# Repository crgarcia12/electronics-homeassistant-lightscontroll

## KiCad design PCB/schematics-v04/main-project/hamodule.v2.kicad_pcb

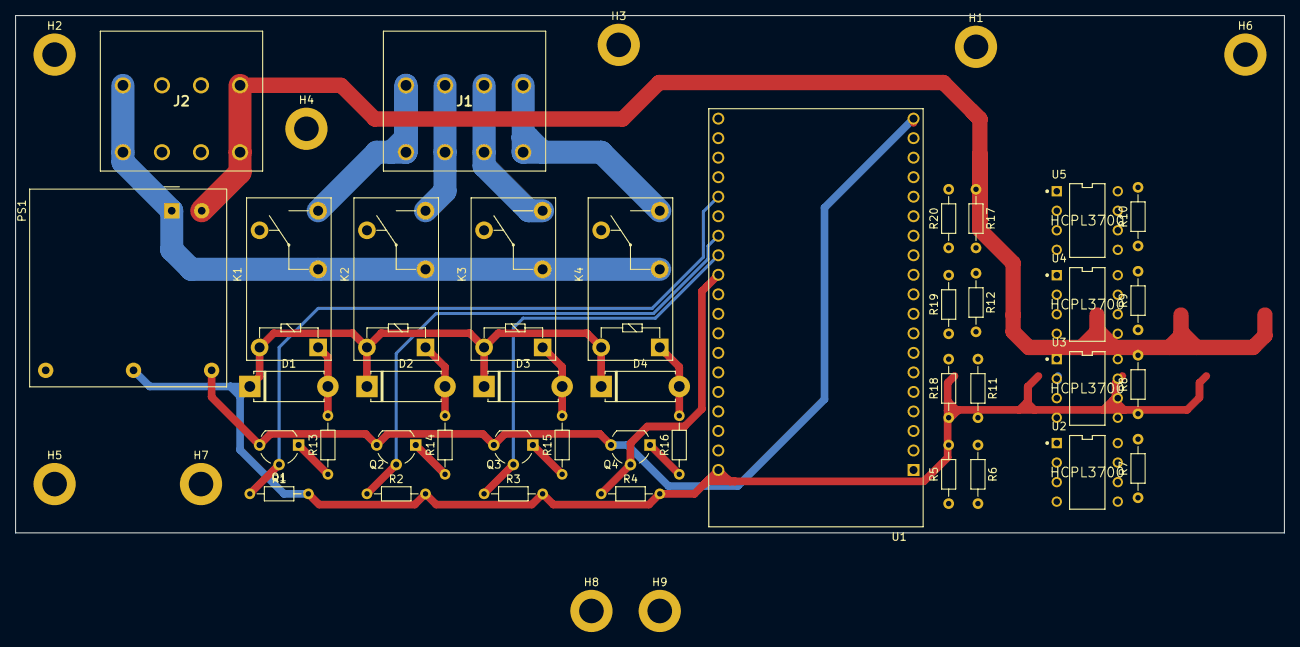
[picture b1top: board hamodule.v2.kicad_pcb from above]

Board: 2 copper layers, 165.1 x 67.3 mm, 49 parts (0 on the bottom side), 34 nets.

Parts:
D1, D2, D3, D4: DIODE; D_5W_P10.16mm_Horizontal
H1, H2, H3, H4, H5, H6, H7, H8, H9: MountingHole_Pad; MountingHole_3.2mm_M3_ISO14580_Pad
J1, J2: 1017505
K1, K2, K3, K4: G5Q-1; Relay_SPDT_Omron-G5Q-1
PS1: RAC05-05SK; Converter_ACDC_RECOM_RAC05-xxSK_THT
Q1, Q2, Q3, Q4: 2N2219; TO-92_Wide
R1, R2, R3, R4, R7, R8, R9, R10: 10K; R_Axial_DIN0204_L3.6mm_D1.6mm_P7.62mm_Horizontal
R5, R6, R11, R12, R17, R18, R19, R20: 47k; R_Axial_DIN0204_L3.6mm_D1.6mm_P7.62mm_Horizontal
R13, R14, R15, R16: 220; R_Axial_DIN0204_L3.6mm_D1.6mm_P7.62mm_Horizontal
U1: ESP32-DEVKITC-32D; MODULE_ESP32-DEVKITC-32D
U2, U3, U4, U5: HCPL3700; ON_Semi-CASE_62605_ISSUE_P-0-0-0

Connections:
3.3V+: R7.2, R8.2, R9.2, R10.2, U1.1, U2.8, U3.8, U4.8, U5.8
5V+: PS1.5, Q1.3, Q2.3, Q3.3, Q4.3, U1.19
5VGND: D1.1, D2.1, D3.1, D4.1, K1.5, K2.5, K3.5, K4.5, PS1.4, R1.2, R2.2, R3.2, R4.2, U1.20, U2.5, U3.5, U4.5, U5.5
220VAC(L): J2.7, J2.8, K1.2, K2.2, K3.2, K4.2, PS1.1
220VAC(N): J2.1, J2.2, PS1.2, U2.1, U3.1, U4.1, U5.1
Earth: H1.1, H2.1, H3.1, H4.1, H5.1, H6.1, H7.1, H8.1, H9.1, J2.3, J2.4, J2.5, J2.6
GPIO32: R9.1, U1.7, U4.6
GPIO33: R10.1, U1.8, U5.6
GPIO34: R7.1, U1.5, U2.6
GPIO35: R8.1, U1.6, U3.6
unnamed: D1.2, K1.1, R13.2
unnamed: D2.2, K2.1, R14.2
unnamed: D3.2, K3.1, R15.2
unnamed: D4.2, K4.1, R16.2
unnamed: Q1.1, R13.1
unnamed: Q1.2, R1.1, U1.34
unnamed: Q2.1, R14.1
unnamed: Q2.2, R2.1, U1.32
unnamed: Q3.1, R15.1
unnamed: Q3.2, R3.1, U1.31
unnamed: Q4.1, R16.1
unnamed: Q4.2, R4.1, U1.30
unnamed: R5.2, R6.1
unnamed: R6.2, U2.4
unnamed: R11.1, R18.2
unnamed: R11.2, U3.4
unnamed: R12.1, R19.2
unnamed: R12.2, U4.4
unnamed: R17.1, R20.2
unnamed: R17.2, U5.4
REO1: J1.7, J1.8, K1.3
REO2: J1.5, J1.6, K2.3
REO3: J1.3, J1.4, K3.3
REO4: J1.1, J1.2, K4.3

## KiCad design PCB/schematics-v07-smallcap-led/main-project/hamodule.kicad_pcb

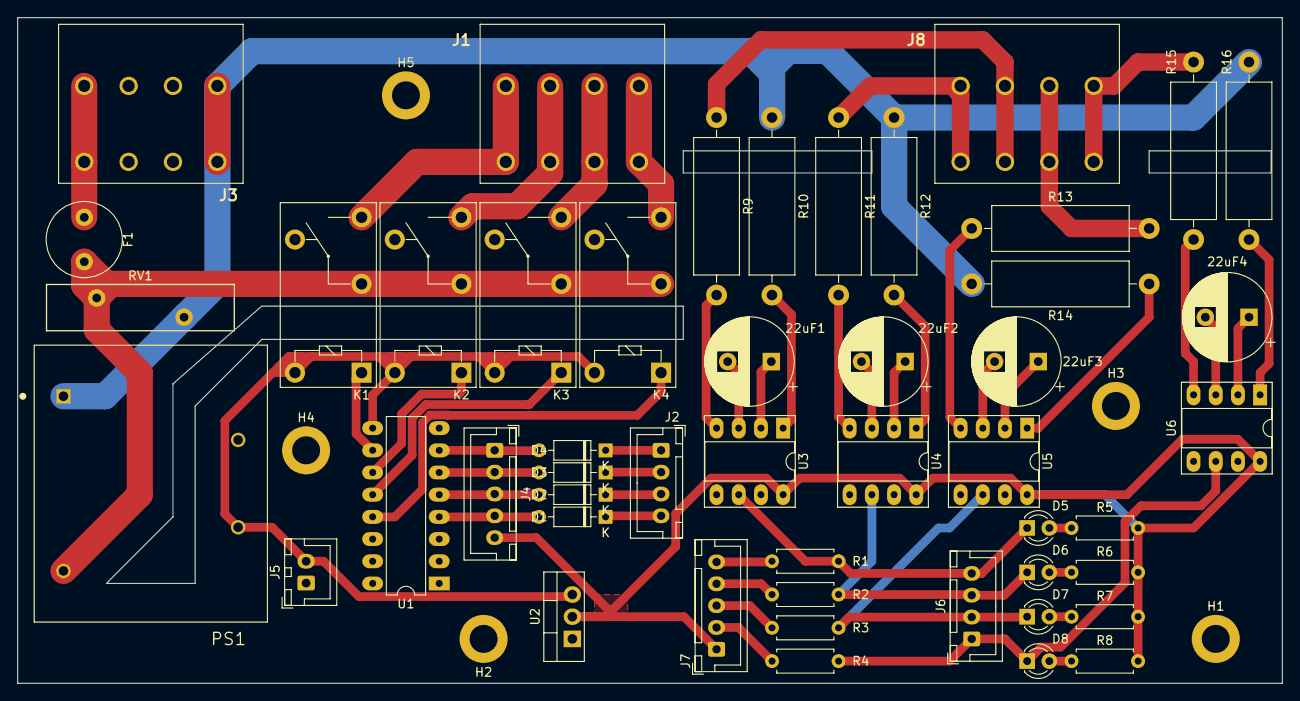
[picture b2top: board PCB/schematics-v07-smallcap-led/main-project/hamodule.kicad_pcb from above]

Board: 2 copper layers, 144.8 x 76.2 mm, 54 parts (0 on the bottom side), 54 nets.

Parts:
22uF1, 22uF2, 22uF3, 22uF4: CP_Small; CP_Radial_D10.0mm_P5.00mm
D1, D2, D3, D4: DIODE; D_DO-35_SOD27_P7.62mm_Horizontal
D5, D6, D7, D8: LED; LED_D3.0mm
F1: Fuse; Fuse_Littelfuse_372_D8.50mm
H1, H2, H3, H4, H5: MountingHole_Pad; MountingHole_3.2mm_M3_ISO14580_Pad
J1, J3, J8: 1017505
J2: Conn-ESP-Relays; JST_XH_B4B-XH-A_1x04_P2.50mm_Vertical
J4: Conn-Buttons; JST_XH_B5B-XH-A_1x05_P2.50mm_Vertical
J5: Conn_01x02; JST_XH_B2B-XH-A_1x02_P2.50mm_Vertical
J6: Conn-Esp-Sensors; JST_XH_B4B-XH-A_1x04_P2.50mm_Vertical
J7: Conn-LedIndicators; JST_XH_B5B-XH-A_1x05_P2.50mm_Vertical
K1, K2, K3, K4: G5Q-1; Relay_SPDT_Omron-G5Q-1
PS1: RAC05-05SK_277; 277
R1, R2, R3, R4, R5, R6, R7, R8: 100; R_Axial_DIN0207_L6.3mm_D2.5mm_P7.62mm_Horizontal
R9, R10, R11, R12, R13, R14, R15, R16: 47k; R_Axial_DIN0516_L15.5mm_D5.0mm_P20.32mm_Horizontal
RV1: Varistor; RV_Disc_D21.5mm_W5.3mm_P10mm
U1: ULN2003A; DIP-16_W7.62mm_LongPads
U2: LD1117S33TR_SOT223; TO-220-3_Vertical
U3, U4, U5, U6: HCPL3700; DIP-8_W7.62mm_Socket_LongPads

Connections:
3.3V+: J4.5, J7.1, R5.2, R6.2, R7.2, R8.2, U2.2, U3.8, U4.8, U5.8, U6.8
5V+: J5.2, K1.5, K2.5, K3.5, K4.5, PS1.7, U1.9, U2.3
220VAC(L): F1.2, K1.2, K2.2, K3.2, K4.2, PS1.5, RV1.2
220VAC(N): J3.1, J3.2, PS1.1, R10.1, R12.1, R14.2, R16.1, RV1.1
EspRel1: D1.2, J4.4, U1.4
EspRel2: D2.2, J4.3, U1.5
EspRel3: D3.2, J4.2, U1.6
EspRel4: D4.2, J4.1, U1.7
EspSens1: D5.1, J6.4, R1.1, U3.6
EspSens2: D6.1, J6.3, R2.1, U4.6
EspSens3: D7.1, J6.2, R3.1, U5.6
EspSens4: D8.1, J6.1, R4.1, U6.6
GND(5V): J5.1, PS1.9, U1.1, U1.2, U1.3, U1.8, U1.14, U1.15, U1.16, U2.1, U3.5, U4.5, U5.5, U6.5
unnamed: 22uF1.1, U3.2
unnamed: 22uF1.2, U3.3
unnamed: 22uF2.1, U4.2
unnamed: 22uF2.2, U4.3
unnamed: 22uF3.1, U5.2
unnamed: 22uF3.2, U5.3
unnamed: 22uF4.1, U6.2
unnamed: 22uF4.2, U6.3
unnamed: D1.1, J2.4
unnamed: D2.1, J2.3
unnamed: D3.1, J2.2
unnamed: D4.1, J2.1
unnamed: D5.2, R5.1
unnamed: D6.2, R6.1
unnamed: D7.2, R7.1
unnamed: D8.2, R8.1
unnamed: F1.1, J3.7, J3.8
unnamed: J7.2, R4.2
unnamed: J7.3, R3.2
unnamed: J7.4, R2.2
unnamed: J7.5, R1.2
unnamed: R9.2, U3.4
unnamed: R10.2, U3.1
unnamed: R11.2, U4.4
unnamed: R12.2, U4.1
unnamed: R13.1, U5.4
unnamed: R14.1, U5.1
unnamed: R15.2, U6.4
unnamed: R16.2, U6.1
REI1: K1.1, U1.10
REI2: K2.1, U1.11
REI3: K3.1, U1.12
REI4: K4.1, U1.13
REO1: J1.7, J1.8, K1.3
REO2: J1.5, J1.6, K2.3
REO3: J1.3, J1.4, K3.3
REO4: J1.1, J1.2, K4.3
Sens1: J8.5, J8.6, R9.1
Sens2: J8.7, J8.8, R11.1
Sens3: J8.3, J8.4, R13.2
Sens4: J8.1, J8.2, R15.1

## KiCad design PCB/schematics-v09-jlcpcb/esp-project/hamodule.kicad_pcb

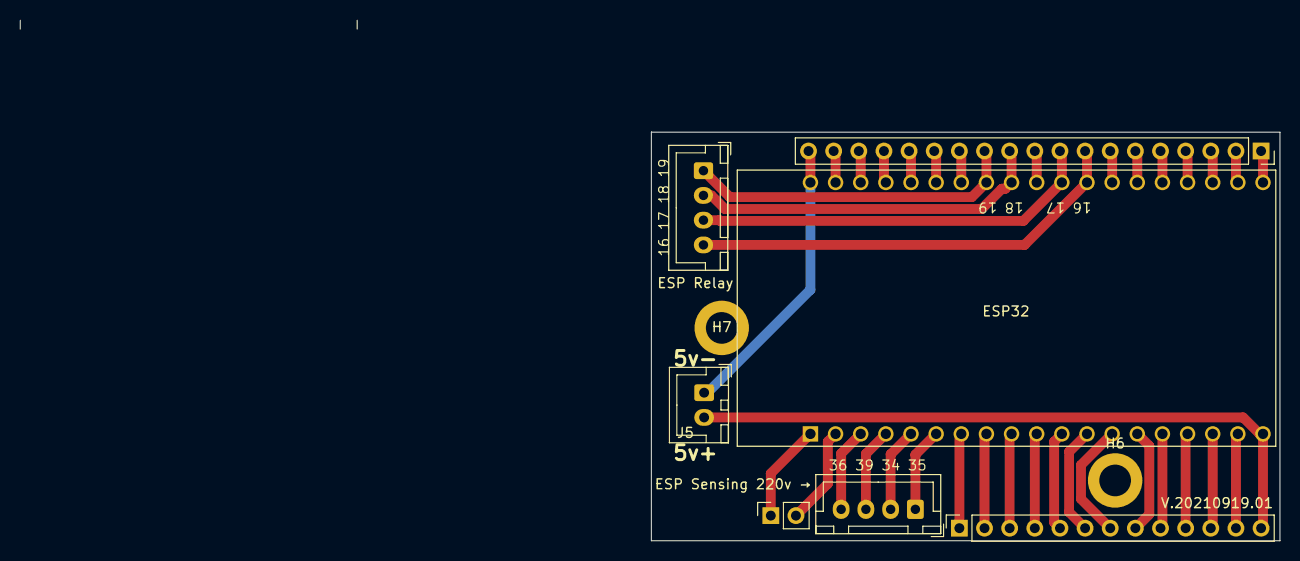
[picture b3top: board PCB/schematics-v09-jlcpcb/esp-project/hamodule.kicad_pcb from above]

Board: 2 copper layers, 63.5 x 41.3 mm, 9 parts (0 on the bottom side), 38 nets.

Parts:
ESP32: ESP32-DEVKITC-32D; MODULE_ESP32-DEVKITC-32D
H6, H7: MountingHole_Pad; MountingHole_3.2mm_M3_ISO14580_Pad
J1: Conn_01x02_Male; PinSocket_1x02_P2.54mm_Vertical
J2: Conn-ESP-Relays; JST_XH_B4B-XH-A_1x04_P2.50mm_Vertical
J3: Conn_01x13_Male; PinSocket_1x13_P2.54mm_Vertical
J4: Conn_01x19_Male; PinSocket_1x19_P2.54mm_Vertical
J5: Conn_01x02; JST_XH_B2B-XH-A_1x02_P2.50mm_Vertical
J6: Conn-Esp-Sensors; JST_XH_B4B-XH-A_1x04_P2.50mm_Vertical

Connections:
5V+: ESP32.19, J3.13, J5.2
GND(5V): ESP32.20, J4.19, J5.1
unnamed: ESP32.1, J1.1
unnamed: ESP32.2, J1.2
unnamed: ESP32.27, J2.1, J4.12
unnamed: ESP32.28, J2.2, J4.11
unnamed: ESP32.30, J2.3, J4.9
unnamed: ESP32.31, J2.4, J4.8
unnamed: ESP32.7, J3.1
unnamed: ESP32.8, J3.2
unnamed: ESP32.9, J3.3
unnamed: ESP32.10, J3.4
unnamed: ESP32.11, J3.5
unnamed: ESP32.12, J3.6
unnamed: ESP32.13, J3.7
unnamed: ESP32.14, J3.8
unnamed: ESP32.15, J3.9
unnamed: ESP32.16, J3.10
unnamed: ESP32.17, J3.11
unnamed: ESP32.18, J3.12
unnamed: ESP32.38, J4.1
unnamed: ESP32.37, J4.2
unnamed: ESP32.36, J4.3
unnamed: ESP32.35, J4.4
unnamed: ESP32.34, J4.5
unnamed: ESP32.33, J4.6
unnamed: ESP32.32, J4.7
unnamed: ESP32.29, J4.10
unnamed: ESP32.26, J4.13
unnamed: ESP32.25, J4.14
unnamed: ESP32.24, J4.15
unnamed: ESP32.23, J4.16
unnamed: ESP32.22, J4.17
unnamed: ESP32.21, J4.18
unnamed: ESP32.6, J6.1
unnamed: ESP32.5, J6.2
unnamed: ESP32.4, J6.3
unnamed: ESP32.3, J6.4

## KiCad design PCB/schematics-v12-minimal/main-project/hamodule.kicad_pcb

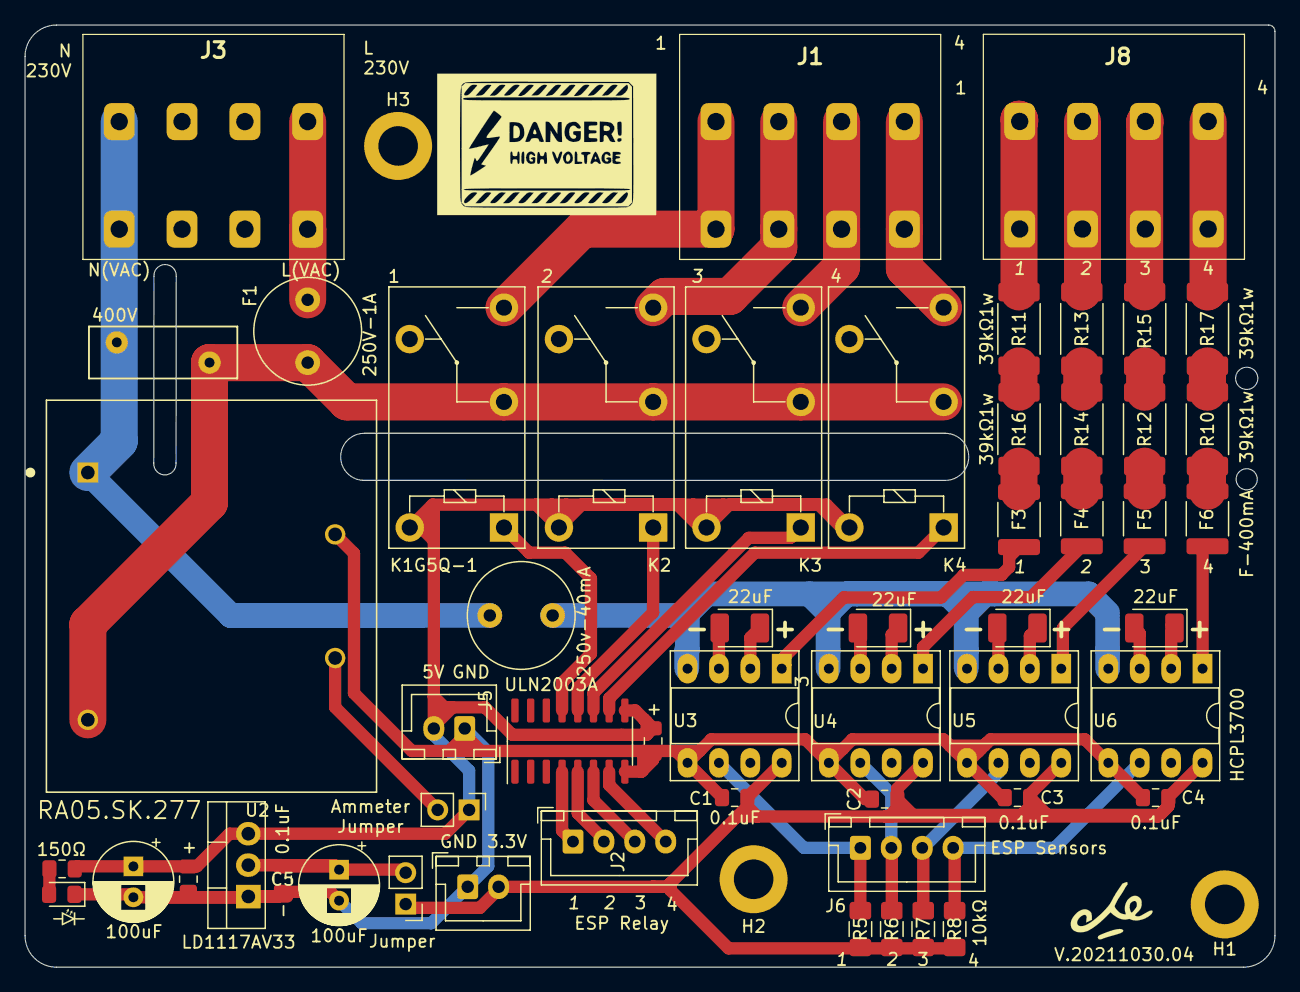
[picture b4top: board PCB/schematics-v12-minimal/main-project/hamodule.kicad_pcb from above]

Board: 2 copper layers, 101.1 x 76.2 mm, 57 parts (0 on the bottom side), 50 nets.

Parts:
22uF1, 22uF2, 22uF3, 22uF4: 22uF; CP_EIA-3528-21_Kemet-B_Pad1.50x2.35mm_HandSolder
100uF_1, 100uF_2: 100uF; CP_Radial_D6.3mm_P2.50mm
C1, C2, C3, C4, C5, C6, C7: 0.1uF; C_0805_2012Metric_Pad1.15x1.40mm_HandSolder
D9: LED; LED_0805_2012Metric_Pad1.15x1.40mm_HandSolder
F1: F250V; Fuse_Littelfuse_372_D8.50mm
F2: 250v-40mA; Fuse_Littelfuse_372_D8.50mm
F3, F4, F5, F6: Fuse; Fuse_1812_4532Metric_Pad1.30x3.40mm_HandSolder
H1, H2, H3: MountingHole_Pad; MountingHole_3.2mm_M3_ISO14580_Pad
J1, J3, J8: 1017505; 1017505_pretty
J2: ESP Relays; JST_XH_B4B-XH-A_1x04_P2.50mm_Vertical
J5: Conn_01x02; JST_XH_B2B-XH-A_1x02_P2.50mm_Vertical
J6: ESP Sensors; JST_XH_B4B-XH-A_1x04_P2.50mm_Vertical
J9, J11: Current Jumper; PinHeader_1x02_P2.54mm_Vertical
J10: GND 3.3V; JST_XH_B2B-XH-A_1x02_P2.50mm_Vertical
K1, K2, K3, K4: G5Q-1; Relay_SPDT_Omron-G5Q-1
R5, R6, R7, R8: 10kΩ; R_1206_3216Metric_Pad1.42x1.75mm_HandSolder
R9: 150Ω; R_0805_2012Metric_Pad1.15x1.40mm_HandSolder
R10, R11, R12, R13, R14, R15, R16, R17: 39kΩ1w; R_2512_6332Metric_Pad1.52x3.35mm_HandSolder
RA05.SK.277: RAC05.05SK.277; 277
RV1: 400V; RV_Disc_D12mm_W4.2mm_P7.5mm
U1: ULN2003A; SOIC-16_3.9x9.9mm_P1.27mm
U2: LD1117S33TR_SOT223; TO-220-3_Vertical
U3, U4, U5, U6: HCPL3700; DIP-8_W7.62mm_Socket_LongPads

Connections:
3.3V+: C1.1, C2.1, C3.1, C4.1, J10.2, J11.1, R5.2, R6.2, R7.2, R8.2, U3.8, U4.8, U5.8, U6.8
5V+: 100uF_1.1, C6.1, C7.1, J5.2, J9.1, K1.5, K2.5, K3.5, K4.5, R9.2, U1.9, U2.3
220VAC(L): F1.2, K1.2, K2.2, K3.2, K4.2, RA05.SK.277.5, RV1.2
220VAC(N): F2.2, U3.4, U4.4, U5.4, U6.4
EspRel1: J2.4, U1.7
EspRel2: J2.3, U1.6
EspRel3: J2.2, U1.5
EspRel4: J2.1, U1.4
EspSens1: J6.4, R8.1, U6.6
EspSens2: J6.3, R7.1, U5.6
EspSens3: J6.2, R6.1, U4.6
EspSens4: J6.1, R5.1, U3.6
GND(5V): 100uF_1.2, 100uF_2.2, C1.2, C2.2, C3.2, C4.2, C5.2, C6.2, C7.2, D9.1, J5.1, J10.1, RA05.SK.277.9, U1.8, U2.1, U3.5, U4.5, U5.5, U6.5
unnamed: 22uF1.1, U3.2
unnamed: 22uF1.2, U3.3
unnamed: 22uF2.1, U4.2
unnamed: 22uF2.2, U4.3
unnamed: 22uF3.1, U5.2
unnamed: 22uF3.2, U5.3
unnamed: 22uF4.1, U6.2
unnamed: 22uF4.2, U6.3
unnamed: 100uF_2.1, C5.1, J11.2, U2.2
unnamed: D9.2, R9.1
unnamed: F1.1, J3.1, J3.2
unnamed: F2.1, J3.7, J3.8, RA05.SK.277.1, RV1.1
unnamed: F3.1, R16.2
unnamed: F3.2, U3.1
unnamed: F4.1, R14.2
unnamed: F4.2, U4.1
unnamed: F5.1, R12.2
unnamed: F5.2, U5.1
unnamed: F6.1, R10.2
unnamed: F6.2, U6.1
unnamed: J9.2, RA05.SK.277.7
unnamed: R10.1, R17.2
unnamed: R11.2, R16.1
unnamed: R12.1, R15.2
unnamed: R13.2, R14.1
REI1: K1.1, U1.13
REI2: K2.1, U1.12
REI3: K3.1, U1.11
REI4: K4.1, U1.10
REO1: J1.7, J1.8, K1.3
REO2: J1.5, J1.6, K2.3
REO3: J1.3, J1.4, K3.3
REO4: J1.1, J1.2, K4.3
Sens1: J8.5, J8.6, R13.1
Sens2: J8.7, J8.8, R11.1
Sens3: J8.3, J8.4, R15.1
Sens4: J8.1, J8.2, R17.1

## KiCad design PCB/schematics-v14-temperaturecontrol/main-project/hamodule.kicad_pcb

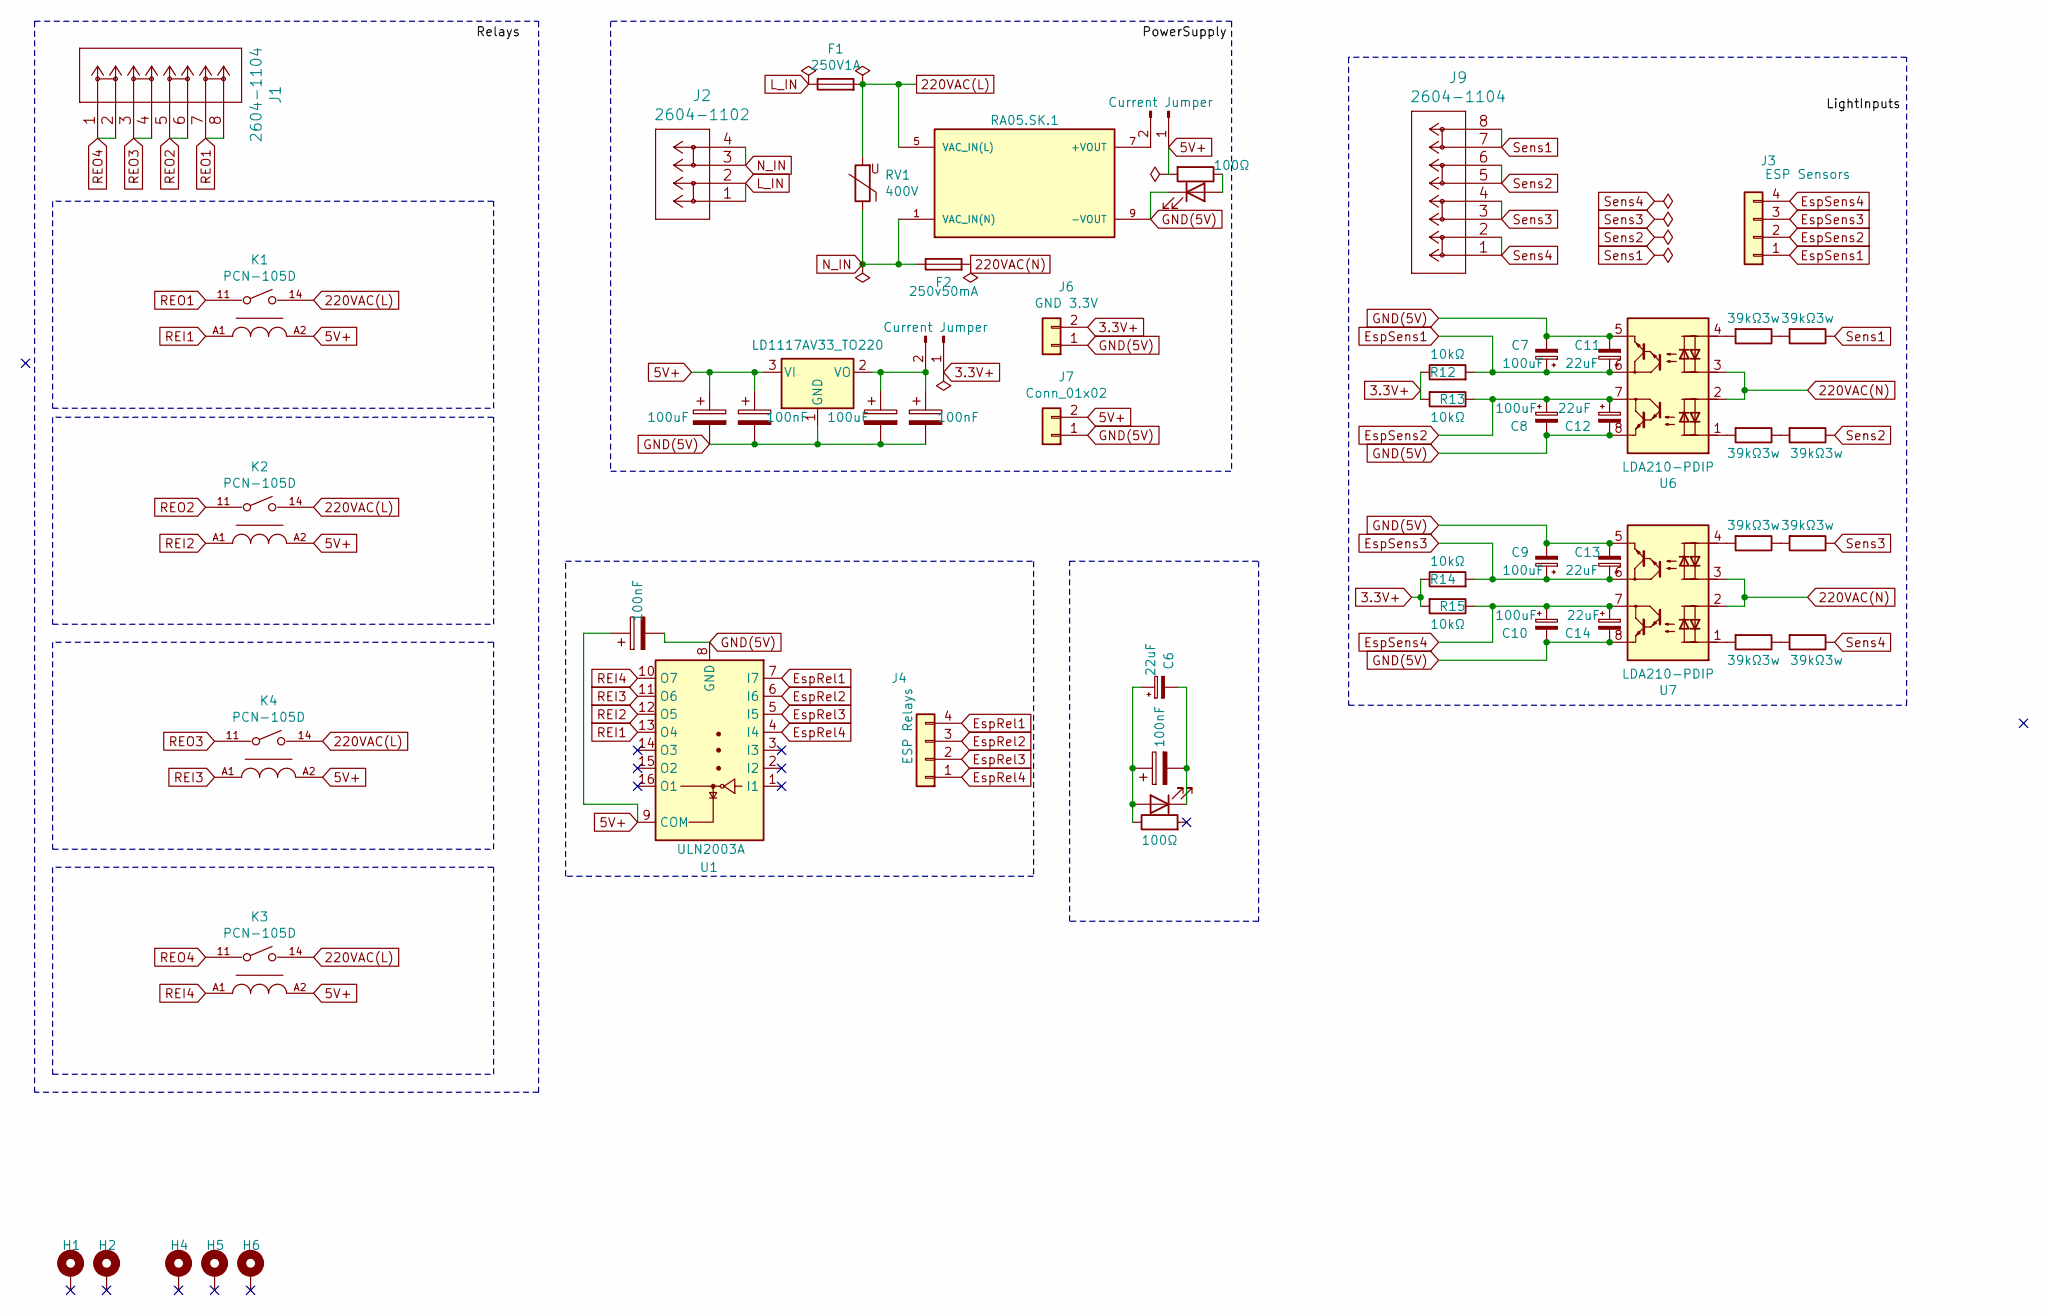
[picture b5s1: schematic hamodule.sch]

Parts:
100uF_1, 100uF_2: 100uF; CP_Radial_D6.3mm_P2.50mm
C1, C2, C3, C5: 100nF; C_0805_2012Metric_Pad1.15x1.40mm_HandSolder; JLCPCB C28233
C6, C11, C12, C13, C14: 22uF; CP_EIA-3528-21_Kemet-B_Pad1.50x2.35mm_HandSolder; JLCPCB C110051
C7, C8, C9, C10: 100uF; C_0805_2012Metric_Pad1.15x1.40mm_HandSolder; JLCPCB C28233
D1, D2: LED; LED_0805_2012Metric_Pad1.15x1.40mm_HandSolder; JLCPCB C2297
F1: 250V1A; Fuse_Littelfuse_372_D8.50mm
F2: 250v50mA; Fuse_Littelfuse_372_D8.50mm
H1, H2, H4, H5, H6: MountingHole_Pad; MountingHole_3.2mm_M3_ISO14580_Pad
J1, J9: 2604-1104; big_pads_2604-1104
J2: 2604-1102; big_pads_2604-1102
J3: ESP Sensors; JST_XH_B4B-XH-A_1x04_P2.50mm_Vertical
J4: ESP Relays; JST_XH_B4B-XH-A_1x04_P2.50mm_Vertical
J5, J8: Current Jumper; PinHeader_1x02_P2.54mm_Vertical
J6: GND 3.3V; JST_XH_B2B-XH-A_1x02_P2.50mm_Vertical
J7: Conn_01x02; JST_XH_B2B-XH-A_1x02_P2.50mm_Vertical
K1, K2, K3, K4: PCN-105D; bigpads_TE_Connectivity-PCN-124D; coil voltage 24V; current rating 3A; mouser part number 655-PCN-124D3MHZ,000; digikey description RELAY GEN PURPOSE SPST 3A 24V
R9, R11: 100Ω; R_0805_2012Metric_Pad1.15x1.40mm_HandSolder; JLCPCB C17408
R12, R13, R14, R15: 10kΩ; R_1206_3216Metric_Pad1.42x1.75mm_HandSolder; JLCPCB C17902
R16, R17, R18, R19, R20, R21, R22, R23: 39kΩ3w; R_2512_6332Metric_Pad1.52x3.35mm_HandSolder; JLCPCB C144424
RA05.SK.1: RAC05.05SK.277; 277; PARTREV N/A
RV1: 400V; RV_Disc_D12mm_W4.2mm_P7.5mm
U1: ULN2003A; SOIC-16_3.9x9.9mm_P1.27mm; JLCPCB C7512
U4: LD1117AV33_TO220; TO-220-3_Vertical
U6, U7: LDA210-PDIP; DIP-8_W7.62mm_Socket_LongPads

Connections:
3.3V+: J5.1, J6.2, R12.1, R13.2, R14.1, R15.2
5V+: 100uF_1.1, C1.1, C2.1, J7.2, J8.1, K1.A2, K2.A2, K3.A2, K4.A2, R11.2, U1.9 (COM), U4.3 (VI)
220VAC(L): F1.2, K1.14, K2.14, K3.14, K4.14, RA05.SK.1.5 (VAC_IN(L)), RV1.2
220VAC(N): F2.2, U6.2, U6.3, U7.2, U7.3
EspRel1: J4.4, U1.7 (I7)
EspRel2: J4.3, U1.6 (I6)
EspRel3: J4.2, U1.5 (I5)
EspRel4: J4.1, U1.4 (I4)
EspSens1: C7.1, C11.1, J3.1, R12.2, U6.6
EspSens2: C8.1, C12.1, J3.2, R13.1, U6.7
EspSens3: C9.1, C13.1, J3.3, R14.2, U7.6
EspSens4: C10.1, C14.1, J3.4, R15.1, U7.7
GND(5V): 100uF_1.2, 100uF_2.2, C1.2, C2.2, C3.2, C7.2, C8.2, C9.2, C10.2, C11.2, C12.2, C13.2, C14.2, D2.1 (K), J6.1, J7.1, RA05.SK.1.9 (-VOUT), U1.8 (GND), U4.1 (GND), U6.5, U6.8, U7.5, U7.8
L_IN: F1.1, J2.1, J2.2
N_IN: F2.1, J2.3, J2.4, RA05.SK.1.1 (VAC_IN(N)), RV1.1
unnamed: 100uF_2.1, C3.1, J5.2, U4.2 (VO)
unnamed: C5.1, C6.1, D1.2 (A), R9.1
unnamed: C5.2, C6.2, D1.1 (K)
unnamed: D2.2 (A), R11.1
unnamed: J8.2, RA05.SK.1.7 (+VOUT)
unnamed: R16.1, R20.2
unnamed: R16.2, U6.4
unnamed: R17.1, R21.2
unnamed: R17.2, U6.1
unnamed: R18.1, R22.2
unnamed: R18.2, U7.4
unnamed: R19.1, R23.2
unnamed: R19.2, U7.1
REI1: K1.A1, U1.13 (O4)
REI2: K2.A1, U1.12 (O5)
REI3: K4.A1, U1.11 (O6)
REI4: K3.A1, U1.10 (O7)
REO1: J1.7, J1.8, K1.11
REO2: J1.5, J1.6, K2.11
REO3: J1.3, J1.4, K4.11
REO4: J1.1, J1.2, K3.11
Sens1: J9.7, J9.8, R20.1
Sens2: J9.5, J9.6, R21.1
Sens3: J9.3, J9.4, R22.1
Sens4: J9.1, J9.2, R23.1

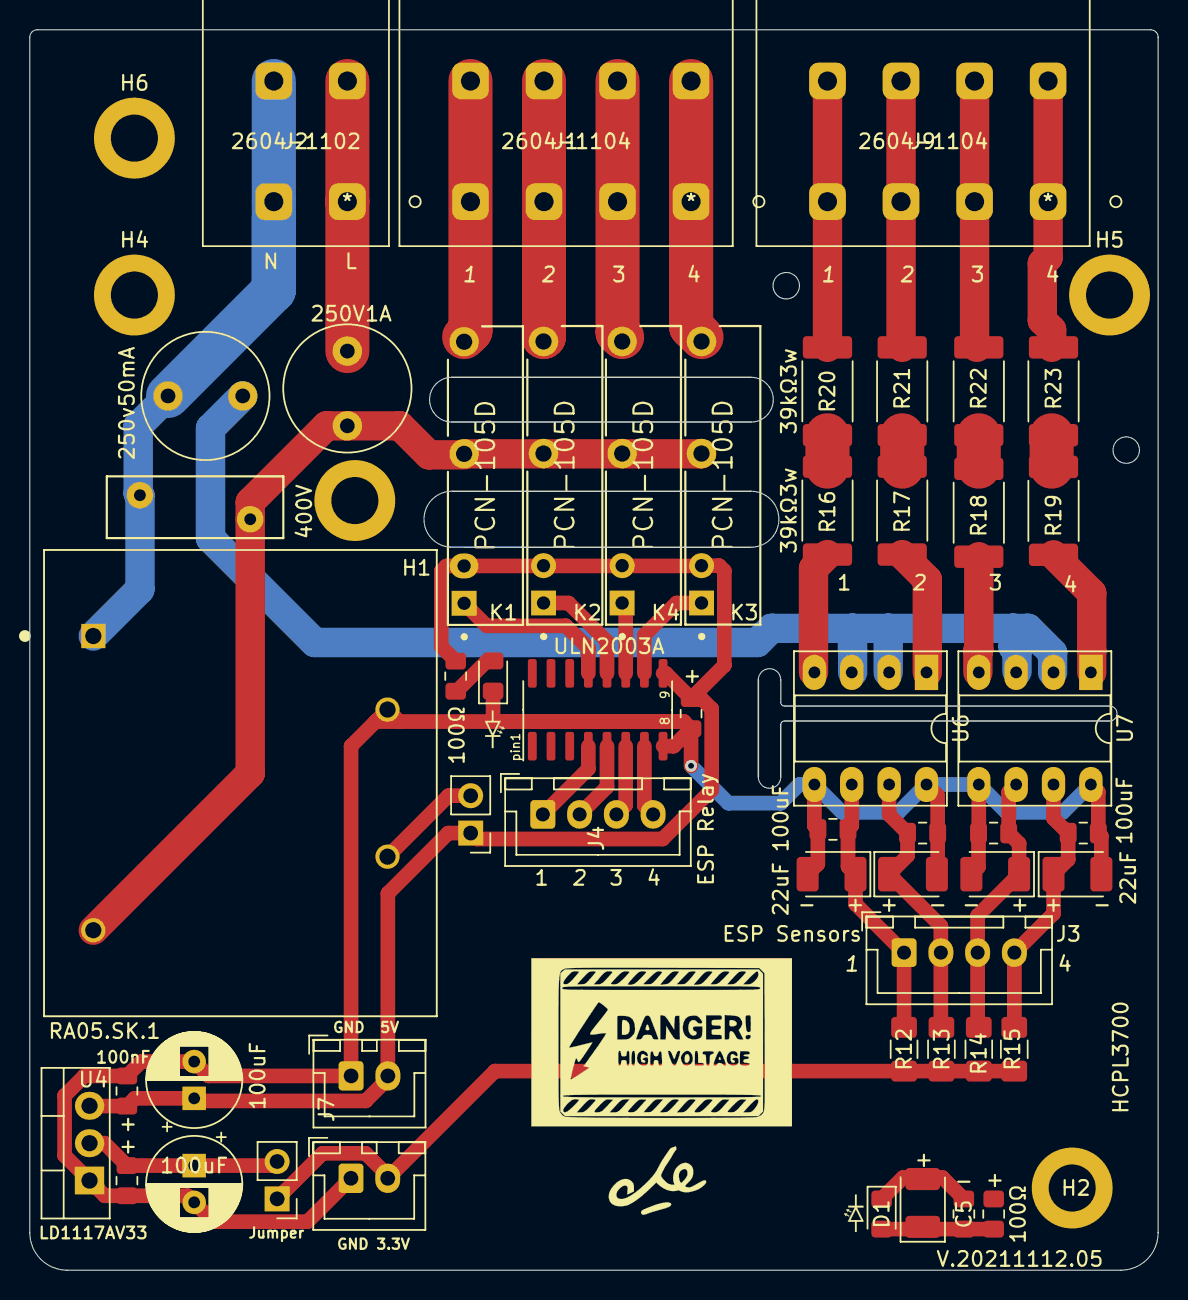
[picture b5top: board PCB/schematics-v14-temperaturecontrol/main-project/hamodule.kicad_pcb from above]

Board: 2 copper layers, 76.7 x 84.3 mm, 57 parts (0 on the bottom side), 40 nets.

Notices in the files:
parts and their libraries:
Copyright 2021 Accelerated Designs. All rights reserved.
